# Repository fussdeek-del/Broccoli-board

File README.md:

# Broccoli Board

> A fully wireless 75% mechanical keyboard built from scratch custom PCB, per-key RGB, BLE 5.0, hot-swap switches, and a 3D printed case. Every component chosen, every trace routed by hand.

---

## What is it?

Broccoli Board is a custom 84-key 75% keyboard I designed completely from scratch. The PCB is designed in KiCad, the case in Fusion 360, and the firmware runs on ZMK. It's fully wireless over BLE 5.0 via the nice!nano V2, has per-key RGB LEDs reverse-mounted on the back of the PCB, and uses Kailh hot-swap sockets so I can swap switches without touching a soldering iron.

## Why i built it?
I didn't want to spend $200+ on a keyboard that still isn't fully mine. So I built one my own that belong to me.

---

## Zine

---

## Gallery

### CAD & Assembly
<table>
  <tr>
    <td></td>
    <td></td>
  </tr>
</table>

### PCB
<table>
  <tr>
    <td></td>
    <td></td>
  </tr>
</table>
---

### PCB Soldered

## Features

- 84 keys, 75% layout
- Wireless BLE 5.0 via nice!nano V2 (nRF52840)
- Per-key SK6812 Mini-E RGB reverse mount on B.Cu
- Kailh hot-swap sockets no soldering to swap switches
- Rotary encoder with push switch (EC11)
- USB-C wired + wireless dual mode
- 3.7V LiPo 2000mAh with MCP73831 charger IC
- 74AHCT125 level shifter for LED data
- USBLC6-2SC6 ESD protection on USB lines
- ZMK firmware
- 2-layer PCB, KiCad 10, JLCPCB fabrication
- Custom 3D printed case tray, plate, and bezel

---

## Hardware Specs

| Component | Details |
|---|---|
| MCU | nice!nano V2 (nRF52840), socketed |
| Layout | 75%, 84 keys |
| Switches | Gateron Blue × 84, 5-pin PCB mount |
| Hotswap | Kailh CPG151101S11 × 84 |
| LEDs | SK6812 Mini-E × 84, reverse mount |
| Encoder | EC11 rotary encoder with push switch |
| Wireless | Bluetooth 5.0 BLE |
| Firmware | ZMK |
| Battery | 3.7V LiPo 2000mAh (804050), JST PH2 |
| Charger IC | MCP73831, 500mA |
| Regulator | ME6211 3.3V LDO |
| Level shifter | 74AHCT125 |
| ESD protection | USBLC6-2SC6 |
| USB connector | GCT USB4105, 16-pin USB-C |
| PCB | 2-layer, JLCPCB, KiCad 10 |
| Case | SLA resin 3D print, Fusion 360 |
| Matrix | 9 rows × 10 columns, col2row |

---

## How to Build

### Order the PCB
1. Go to [JLCPCB](https://jlcpcb.com)
2. Upload `pcb/gerbers.zip`
3. 2-layer, FR-4, 1.6mm, HASL or ENIG
4. Minimum order 5 boards

### Flash the Firmware
1. Fork the [ZMK firmware repo](https://github.com/fussdeek-del/Broccoli--board-zmk)
2. Edit keymap at `boards/shields/broccoli_board/broccoli_board.keymap`
3. Push GitHub Actions builds automatically
4. Download `.uf2` from Actions artifacts
5. Double-tap reset on nice!nano to enter bootloader
6. Drag `.uf2` onto the USB drive that appears

note: The frimware isn't completely, i will complete it once this gets approved.

### Assembly Notes
- Solder LEDs on **B.Cu** reverse mount facing down
- Solder hotswap sockets on **F.Cu**
- Solder the nice!nano v2
- Battery connects via JST PH2 to J2

## BOM

> 💰 Estimated total: **~$174 USD** — can drop to **$120–$140** buying locally.

| Component | Spec | Qty | Price | Notes | Link |
|---|---|---|---|---|---|
| Microcontroller (MCU) | nice!nano V2 nRF52840 | ×1 | $7.00 | Clone — cheaper, slightly less reliable | [Buy](https://www.aliexpress.com/item/1005006271881076.html) |
| 74AHCT125 Level Shifter | TSSOP-14 | ×1 | $2.52 | Pack of 10 — LED data 3.3V→5V | [Buy](https://www.aliexpress.com/item/1005008171122183.html) |
| MCP73831 LiPo Charger | SOT-23-5 | ×1 | $2.50 | Pack of 10 — LiPo charging IC | [Buy](https://www.aliexpress.com/item/1005007439657191.html) |
| ME6211 3.3V LDO | ME6211C33 SOT-23-5 | ×1 | $2.20 | Pack of 10 — 3.3V regulator | [Buy](https://www.aliexpress.com/item/1005007315116858.html) |
| USBLC6-2SC6 ESD Protection | SOT-23-6 | ×1 | $1.50 | Pack of 10 — USB ESD protection | [Buy](https://www.aliexpress.com/item/32807108222.html) |
| Gateron Blue Switch | G Pro Blue 5-pin | ×84 | $24.00 | Pack of 100 — 5-pin PCB mount | [Buy](https://www.aliexpress.com/item/1005006091988869.html) |
| Kailh Hotswap Socket | MX compatible | ×84 | $7.00 | Pack of 100 | [Buy](https://www.aliexpress.com/item/1005006105603269.html) |
| EC11 Rotary Encoder | 20mm with push switch | ×1 | $2.00 | Pack of 5 | [Buy](https://www.aliexpress.com/item/1005006460161288.html) |
| Reset Button | SMD tactile 3×4mm | ×1 | $1.50 | Pack of 30 | [Buy](https://www.aliexpress.com/item/4001107416458.html) |
| SK6812 Mini-E RGB LED | Reverse mount | ×84 | $13.50 | Pack of 100 — buy 100, need 84 + spares | [Buy](https://www.aliexpress.com/item/1005004249903121.html) |
| 1N4148W Matrix Diode | SOD-123 | ×84 | $1.50 | Pack of 100 — buy 100, need 84 + spares | [Buy](https://www.aliexpress.com/item/1005010728396328.html) |
| Resistor 10K | 0603 | ×10 | $1.20 | Pack of 300 | [Buy](https://www.aliexpress.com/item/1005011779883974.html) |
| Resistor 5.1K | 0603 | ×5 | $1.30 | Pack of 300 | [Buy](https://www.aliexpress.com/item/1005011779883974.html) |
| Resistor 330Ω | 0603 | ×1 | $2.00 | Pack of 500 | [Buy](https://www.aliexpress.com/item/1005005700395390.html) |
| Capacitor 100nF | 0805 | ×100 | $2.00 | Pack of 200 | [Buy](https://www.aliexpress.com/item/1005007660078779.html) |
| Capacitor 10µF | 0805 | ×1 | $2.20 | Pack of 200 | [Buy](https://www.aliexpress.com/item/1005007660078779.html) |
| USB-C Receptacle 16P | GCT USB4105 SMD | ×1 | $4.50 | Pack of 5 | [Buy](https://www.aliexpress.com/item/1005005581945089.html) |
| JST PH2 2-pin | PH2.0 2-pin connector | ×1 | $2.00 | Pack of 2 | [Buy](https://www.aliexpress.com/item/1005010615395743.html) |
| Polyfuse 500mA | Resettable fuse 1206 | ×1 | $1.70 | Pack of 10 | [Buy](https://www.aliexpress.com/item/1005005235906949.html) |
| LiPo 3.7V 2000mAh | 804050, JST PH | ×1 | $9.40 | Price for 2 | [Buy](https://www.aliexpress.com/item/1005005984841109.html) |
| Keycap Set | PBT 75% MX compatible | ×75 | $22.50 | 100+ keycaps included | [Buy](https://www.aliexpress.com/item/1005007416863215.html) |
| Rotary Knob | Aluminum 6mm D shaft 20mm | ×1 | $2.00 | 2 pieces | [Buy](https://www.aliexpress.com/item/4001091267351.html) |
| PCB Fabrication | 2-layer, FR-4, 1.6mm, HASL | ×5 boards | $22.20 | Minimum 5 pieces | [JLCPCB](https://cart.jlcpcb.com/quote) |
| 3D Print — Tray | SLA resin | ×1 | $25.30 | Local 3D printer recommended | [JLC3DP](https://jlc3dp.com/3d-printing-quote) |
| 3D Print — Top Plate | SLA resin | ×1 | $8.30 | Local 3D printer recommended | [JLC3DP](https://jlc3dp.com/3d-printing-quote) |
| 3D Print — Top Cover | SLA resin | ×1 | $2.65 | Local 3D printer recommended | [JLC3DP](https://jlc3dp.com/3d-printing-quote) |
| M3 Screws | M3 × 8mm countersunk | ×10 | $1.00 | Pack of 50 | [Buy](https://www.aliexpress.com/item/1005008810897680.html) |
| M3 Standoffs | M3 × 4mm | ×10 | $1.00 | Pack of 50 | [Buy](https://www.aliexpress.com/item/1005008810897680.html) |

---
## Schematics note
Schematics is reviewed my multiple people in fallout + AI. there was problem init that i fixed, and now it LGTM
repo is surface checked by riitam
## Credits

- [KiCad](https://www.kicad.org/) — PCB design
- [ZMK Firmware](https://zmk.dev/) — open source keyboard firmware
- [Fusion 360](https://www.autodesk.com/products/fusion-360/) — case design
- [nice!nano](https://nicekeyboards.com/nice-nano/) — nRF52840 BLE module
- [Hack Club Fallout](https://fallout.hackclub.com) — grant that made this real

Made by **Nabeel Ahmed (18) × Hashir (17)** — Punjab, Pakistan 🇵🇰 BWP

---

## License

MIT

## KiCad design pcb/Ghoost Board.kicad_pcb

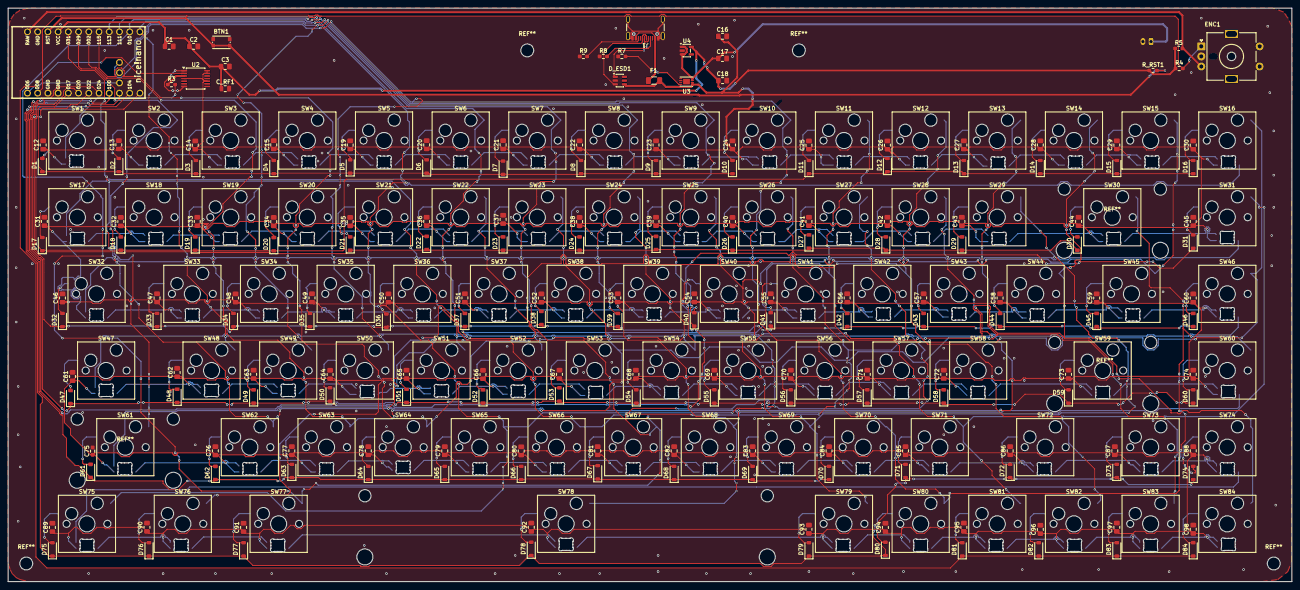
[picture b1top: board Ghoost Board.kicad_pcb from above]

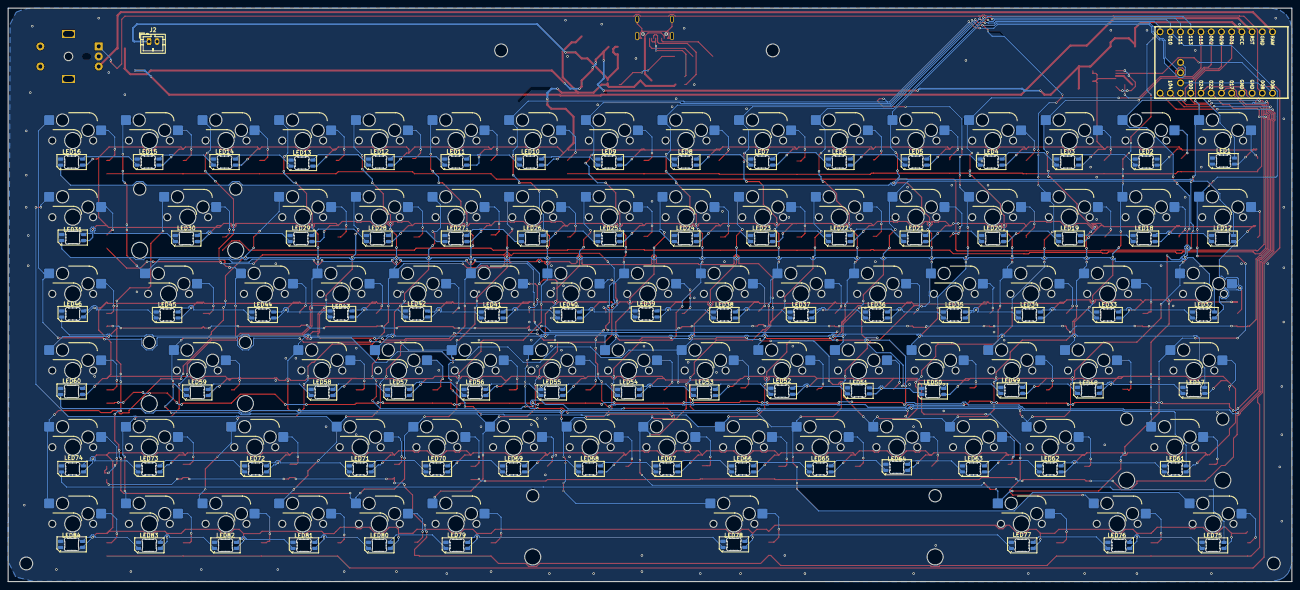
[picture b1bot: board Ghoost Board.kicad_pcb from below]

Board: 2 copper layers, 319.0 x 142.5 mm, 360 parts (85 on the bottom side), 201 nets.

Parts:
BTN1: RESET; SW_Push_1P1T_NO_CK_KMR2
C1, C2, C3, C17, C18: 100nF; C_0805_2012Metric_Pad1.18x1.45mm_HandSolder
C12, C13, C14, C15, C16, C19, C20, C21, C22, C23, C24, C25, C26, C27, C28, C29, C30, C31, C32, C33, C34, C35, C36, C37, C38, C39, C40, C41, C42, C43, C44, C45, C46, C47, C48, C49, C50, C51, C52, C53, C54, C55, C56, C57, C58, C59, C60, C61, C62, C63, C64, C65, C66, C67, C68, C69, C70, C71, C72, C73, C74, C76, C77, C78, C79, C80, C81, C82, C83, C84, C85, C86, C87, C88, C89, C90, C91, C92, C93, C94, C95, C96, C97, C98: 100nf; C_0805_2012Metric_Pad1.18x1.45mm_HandSolder
C75: 100nf; R_0603_1608Metric_Pad0.98x0.95mm_HandSolder
C_RF1: 10uF; C_0805_2012Metric
D1, D2, D3, D4, D5, D6, D7, D8, D9, D10, D11, D12, D13, D14, D15, D16, D17, D18, D19, D20, D21, D22, D23, D24, D25, D26, D27, D28, D29, D30, D31, D32, D33, D34, D35, D36, D37, D38, D39, D40, D41, D42, D43, D44, D45, D46, D47, D48, D49, D50, D51, D52, D53, D54, D55, D56, D57, D58, D59, D60, D61, D62, D63, D64, D65, D66, D67, D68, D69, D70, D71, D72, D73, D74, D75, D76, D77, D78, D79, D80, D81, D82, D83, D84: 1N4148W; D_SOD-123
D_ESD1: USBLC6-2SC6; SOT-23-6
ENC1: EC11; RotaryEncoder_Alps_EC11E-Switch_Vertical_H20mm_MountingHoles
F1: 500mA; Fuse_1206_3216Metric
J1: USB_C_Receptacle_USB2.0_16P; USB_C_Receptacle_GCT_USB4105-xx-A_16P_TopMnt_Horizontal
J2: Battery_JST_PH2; JST_PH_B2B-PH-K_1x02_P2.00mm_Vertical
LED1, LED2, LED3, LED4, LED5, LED6, LED7, LED8, LED9, LED10, LED11, LED12, LED13, LED14, LED15, LED16, LED17, LED18, LED19, LED20, LED21, LED22, LED23, LED24, LED25, LED26, LED27, LED28, LED29, LED30, LED31, LED32, LED33, LED34, LED35, LED36, LED37, LED38, LED39, LED40, LED41, LED42, LED43, LED44, LED45, LED46, LED47, LED48, LED49, LED50, LED51, LED52, LED53, LED54, LED55, LED56, LED57, LED58, LED59, LED60, LED61, LED62, LED63, LED64, LED65, LED66, LED67, LED68, LED69, LED70, LED71, LED72, LED73, LED74, LED75, LED76, LED77, LED78, LED79, LED80, LED81, LED82, LED83, LED84: SK6812Mini-E; LED_SK6812MINI-E_3.2x2.8mm_P1.5mm_ReverseMount
R3: 330R; R_0603_1608Metric_Pad0.98x0.95mm_HandSolder
R4, R5, R7: 10K; R_0603_1608Metric_Pad0.98x0.95mm_HandSolder
R8: 5.1K; R_0603_1608Metric_Pad0.98x0.95mm_HandSolder
R9: 5.1k; R_0603_1608Metric_Pad0.98x0.95mm_HandSolder
R_RST1: 10K; R_0603_1608Metric_Pad0.98x0.95mm_HandSolder
SW1, SW2, SW3, SW4, SW5, SW6, SW7, SW8, SW9, SW10, SW11, SW12, SW13, SW14, SW15, SW16, SW17, SW18, SW19, SW20, SW21, SW22, SW23, SW24, SW25, SW26, SW27, SW28, SW29, SW30, SW31, SW32, SW33, SW34, SW35, SW36, SW37, SW38, SW39, SW40, SW41, SW42, SW43, SW44, SW45, SW46, SW47, SW48, SW49, SW50, SW51, SW52, SW53, SW54, SW55, SW56, SW57, SW58, SW59, SW60, SW61, SW62, SW63, SW64, SW65, SW66, SW67, SW68, SW69, SW70, SW71, SW72, SW73, SW74, SW75, SW76, SW77, SW78, SW79, SW80, SW81, SW82, SW83, SW84: Gateron_Blue; SW_Hotswap_Kailh_MX_1.00u
U1: nice!nano; nice_nano
U2: 74AHCT125; TSSOP-14_4.4x5mm_P0.65mm
U3: MCP73831; DFN-8-1EP_3x2mm_P0.5mm_EP1.7x1.4mm
U4: ME6211-3.3V; SOT-23-5

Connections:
+3.3V: C1.1, C2.1, C3.1, C18.1, C_RF1.1, R4.1, R5.1, R_RST1.1, U1.21 (VCC), U4.5 (V_{OUT})
/COL0: SW1.2, SW11.2, SW21.2, SW31.2, SW41.2, SW51.2, SW61.2, SW71.2, SW81.2, U1.20 (AIN7/P0.31)
/COL1: SW2.2, SW12.2, SW22.2, SW32.2, SW42.2, SW52.2, SW62.2, SW72.2, SW82.2, U1.19 (AIN5/P0.29)
/COL2: SW3.2, SW13.2, SW23.2, SW33.2, SW43.2, SW53.2, SW63.2, SW73.2, SW83.2, U1.18 (AIN0/P0.02)
/COL3: SW4.2, SW14.2, SW24.2, SW34.2, SW44.2, SW54.2, SW64.2, SW74.2, SW84.2, U1.17 (P1.15)
/COL4: SW5.2, SW15.2, SW25.2, SW35.2, SW45.2, SW55.2, SW65.2, SW75.2, U1.16 (P1.13)
/COL5: SW6.2, SW16.2, SW26.2, SW36.2, SW46.2, SW56.2, SW66.2, SW76.2, U1.15 (P1.11)
/COL6: SW7.2, SW17.2, SW27.2, SW37.2, SW47.2, SW57.2, SW67.2, SW77.2, U1.14 (NFC2/P0.10)
/COL7: SW8.2, SW18.2, SW28.2, SW38.2, SW48.2, SW58.2, SW68.2, SW78.2, U1.13 (NFC1/P0.09)
/COL8: SW9.2, SW19.2, SW29.2, SW39.2, SW49.2, SW59.2, SW69.2, SW79.2, U1.32 (P1.02)
/COL9: SW10.2, SW20.2, SW30.2, SW40.2, SW50.2, SW60.2, SW70.2, SW80.2, U1.33 (P1.07)
/ENC_A: ENC1.A, R4.2, U1.2 (RX1/P0.08)
/ENC_B: ENC1.B, R5.2, U1.24 (BATIN/P0.04)
/LED sheets/LED2_DOUT: LED2.1 (DOUT), LED3.3 (DIN)
/LED sheets/LED3_DOUT: LED3.1 (DOUT), LED4.3 (DIN)
/LED sheets/LED4_DOUT: LED4.1 (DOUT), LED5.3 (DIN)
/LED sheets/LED5_DOUT: LED5.1 (DOUT), LED6.3 (DIN)
/LED sheets/LED6_DOUT: LED6.1 (DOUT), LED7.3 (DIN)
/LED sheets/LED7_DOUT: LED7.1 (DOUT), LED8.3 (DIN)
/LED sheets/LED8_DOUT: LED8.1 (DOUT), LED9.3 (DIN)
/LED sheets/LED9_DOUT: LED9.1 (DOUT), LED10.3 (DIN)
/LED sheets/LED10_DOUT: LED10.1 (DOUT), LED11.3 (DIN)
/LED sheets/LED11_DOUT: LED11.1 (DOUT), LED12.3 (DIN)
/LED sheets/LED12_DOUT: LED12.1 (DOUT), LED13.3 (DIN)
/LED sheets/LED13_DOUT: LED13.1 (DOUT), LED14.3 (DIN)
/LED sheets/LED14_DOUT: LED14.1 (DOUT), LED15.3 (DIN)
/LED sheets/LED15_DOUT: LED15.1 (DOUT), LED16.3 (DIN)
/LED sheets/LED16_DOUT: LED16.1 (DOUT), LED17.3 (DIN)
/LED sheets/LED17_DOUT: LED17.1 (DOUT), LED18.3 (DIN)
/LED sheets/LED18_DOUT: LED18.1 (DOUT), LED19.3 (DIN)
/LED sheets/LED19_DOUT: LED19.1 (DOUT), LED20.3 (DIN)
/LED sheets/LED20_DOUT: LED20.1 (DOUT), LED21.3 (DIN)
/LED sheets/LED21_DOUT: LED21.1 (DOUT), LED22.3 (DIN)
/LED sheets/LED22_DOUT: LED22.1 (DOUT), LED23.3 (DIN)
/LED sheets/LED23_DOUT: LED23.1 (DOUT), LED24.3 (DIN)
/LED sheets/LED24_DOUT: LED24.1 (DOUT), LED25.3 (DIN)
/LED sheets/LED25_DOUT: LED25.1 (DOUT), LED26.3 (DIN)
/LED sheets/LED26_DOUT: LED26.1 (DOUT), LED27.3 (DIN)
/LED sheets/LED27_DOUT: LED27.1 (DOUT), LED28.3 (DIN)
/LED sheets/LED28_DOUT: LED28.1 (DOUT), LED29.3 (DIN)
/LED sheets/LED29_DOUT: LED29.1 (DOUT), LED30.3 (DIN)
/LED sheets/LED30_DOUT: LED30.1 (DOUT), LED31.3 (DIN)
/LED sheets/LED31_DOUT: LED31.1 (DOUT), LED32.3 (DIN)
/LED sheets/LED32_DOUT: LED32.1 (DOUT), LED33.3 (DIN)
/LED sheets/LED33_DOUT: LED33.1 (DOUT), LED34.3 (DIN)
/LED sheets/LED34_DOUT: LED34.1 (DOUT), LED35.3 (DIN)
/LED sheets/LED35_DOUT: LED35.1 (DOUT), LED36.3 (DIN)
/LED sheets/LED36_DOUT: LED36.1 (DOUT), LED37.3 (DIN)
/LED sheets/LED37_DOUT: LED37.1 (DOUT), LED38.3 (DIN)
/LED sheets/LED38_DOUT: LED38.1 (DOUT), LED39.3 (DIN)
/LED sheets/LED39_DOUT: LED39.1 (DOUT), LED40.3 (DIN)
/LED sheets/LED40_DOUT: LED40.1 (DOUT), LED41.3 (DIN)
/LED sheets/LED41_DOUT: LED41.1 (DOUT), LED42.3 (DIN)
/LED sheets/LED42_DOUT: LED42.1 (DOUT), LED43.3 (DIN)
/LED sheets/LED43_DOUT: LED43.1 (DOUT), LED44.3 (DIN)
/LED sheets/LED44_DOUT: LED44.1 (DOUT), LED45.3 (DIN)
/LED sheets/LED45_DOUT: LED45.1 (DOUT), LED46.3 (DIN)
/LED sheets/LED46_DOUT: LED46.1 (DOUT), LED47.3 (DIN)
/LED sheets/LED47_DOUT: LED47.1 (DOUT), LED48.3 (DIN)
/LED sheets/LED48_DOUT: LED48.1 (DOUT), LED49.3 (DIN)
/LED sheets/LED49_DOUT: LED49.1 (DOUT), LED50.3 (DIN)
/LED sheets/LED50_DOUT: LED50.1 (DOUT), LED51.3 (DIN)
/LED sheets/LED51_DOUT: LED51.1 (DOUT), LED52.3 (DIN)
/LED sheets/LED52_DOUT: LED52.1 (DOUT), LED53.3 (DIN)
/LED sheets/LED53_DOUT: LED53.1 (DOUT), LED54.3 (DIN)
/LED sheets/LED54_DOUT: LED54.1 (DOUT), LED55.3 (DIN)
/LED sheets/LED55_DOUT: LED55.1 (DOUT), LED56.3 (DIN)
/LED sheets/LED56_DOUT: LED56.1 (DOUT), LED57.3 (DIN)
/LED sheets/LED57_DOUT: LED57.1 (DOUT), LED58.3 (DIN)
/LED sheets/LED58_DOUT: LED58.1 (DOUT), LED59.3 (DIN)
/LED sheets/LED59_DOUT: LED59.1 (DOUT), LED60.3 (DIN)
/LED sheets/LED60_DOUT: LED60.1 (DOUT), LED61.3 (DIN)
/LED sheets/LED61_DOUT: LED61.1 (DOUT), LED62.3 (DIN)
/LED sheets/LED62_DOUT: LED62.1 (DOUT), LED63.3 (DIN)
/LED sheets/LED63_DOUT: LED63.1 (DOUT), LED64.3 (DIN)
/LED sheets/LED64_DOUT: LED64.1 (DOUT), LED65.3 (DIN)
/LED sheets/LED65_DOUT: LED65.1 (DOUT), LED66.3 (DIN)
/LED sheets/LED66_DOUT: LED66.1 (DOUT), LED67.3 (DIN)
/LED sheets/LED67_DOUT: LED67.1 (DOUT), LED68.3 (DIN)
/LED sheets/LED68_DOUT: LED68.1 (DOUT), LED69.3 (DIN)
/LED sheets/LED69_DOUT: LED69.1 (DOUT), LED70.3 (DIN)
/LED sheets/LED70_DOUT: LED70.1 (DOUT), LED71.3 (DIN)
/LED sheets/LED71_DOUT: LED71.1 (DOUT), LED72.3 (DIN)
/LED sheets/LED72_DOUT: LED72.1 (DOUT), LED73.3 (DIN)
/LED sheets/LED73_DOUT: LED73.1 (DOUT), LED74.3 (DIN)
/LED sheets/LED74_DOUT: LED74.1 (DOUT), LED75.3 (DIN)
/LED sheets/LED75_DOUT: LED75.1 (DOUT), LED76.3 (DIN)
/LED sheets/LED76_DOUT: LED76.1 (DOUT), LED77.3 (DIN)
/LED sheets/LED77_DOUT: LED77.1 (DOUT), LED78.3 (DIN)
/LED sheets/LED78_DOUT: LED78.1 (DOUT), LED79.3 (DIN)
/LED sheets/LED79_DOUT: LED79.1 (DOUT), LED80.3 (DIN)
/LED sheets/LED80_DOUT: LED80.1 (DOUT), LED81.3 (DIN)
/LED sheets/LED81_DOUT: LED81.1 (DOUT), LED82.3 (DIN)
/LED sheets/LED82_DOUT: LED82.1 (DOUT), LED83.3 (DIN)
/LED sheets/LED83_DOUT: LED83.1 (DOUT), LED84.3 (DIN)
/LED_DATA_3V3: U1.1 (TX0/P0.06), U2.2
/LED_DATA_5V: R3.1, U2.3
/LED_DATA_OUT: LED1.3 (DIN), R3.2
/RESET: BTN1.2, R_RST1.2, U1.22 (RST)
/ROW0: D1.1 (K), D2.1 (K), D3.1 (K), D4.1 (K), D5.1 (K), D6.1 (K), D7.1 (K), D8.1 (K), D9.1 (K), D10.1 (K), U1.5 (P0.17)
/ROW1: D11.1 (K), D12.1 (K), D13.1 (K), D14.1 (K), D15.1 (K), D16.1 (K), D17.1 (K), D18.1 (K), D19.1 (K), D20.1 (K), U1.6 (P0.20)
/ROW2: D21.1 (K), D22.1 (K), D23.1 (K), D24.1 (K), D25.1 (K), D26.1 (K), D27.1 (K), D28.1 (K), D29.1 (K), D30.1 (K), U1.7 (P0.22)
/ROW3: D31.1 (K), D32.1 (K), D33.1 (K), D34.1 (K), D35.1 (K), D36.1 (K), D37.1 (K), D38.1 (K), D39.1 (K), D40.1 (K), U1.8 (P0.24)
/ROW4: D41.1 (K), D42.1 (K), D43.1 (K), D44.1 (K), D45.1 (K), D46.1 (K), D47.1 (K), D48.1 (K), D49.1 (K), D50.1 (K), U1.9 (P1.00)
/ROW5: D51.1 (K), D52.1 (K), D53.1 (K), D54.1 (K), D55.1 (K), D56.1 (K), D57.1 (K), D58.1 (K), D59.1 (K), D60.1 (K), U1.10 (P0.11)
/ROW6: D61.1 (K), D62.1 (K), D63.1 (K), D64.1 (K), D65.1 (K), D66.1 (K), D67.1 (K), D68.1 (K), D69.1 (K), D70.1 (K), U1.11 (P1.04)
/ROW7: D71.1 (K), D72.1 (K), D73.1 (K), D74.1 (K), D75.1 (K), D76.1 (K), D77.1 (K), D78.1 (K), D79.1 (K), D80.1 (K), U1.12 (P1.06)
/ROW8: D81.1 (K), D82.1 (K), D83.1 (K), D84.1 (K), U1.31 (P1.01)
/USB_DN: D_ESD1.1 (I/O1), J1.A7 (D-), J1.B7 (D-)
/USB_DP: D_ESD1.3 (I/O2), J1.A6 (D+), J1.B6 (D+)
/VBAT: C17.1, J2.1, U3.3 (V_{BAT}), U3.4 (V_{BAT}), U4.1 (V_{IN}), U4.3 (CE)
/VBUS_IN: F1.1, J1.A4 (VBUS), J1.A9 (VBUS), J1.B4 (VBUS), J1.B9 (VBUS)
GND: BTN1.1, C1.2, C2.2, C3.2, C12.2, C13.2, C14.2, C15.2, C16.2, C17.2, C18.2, C19.2, C20.2, C21.2, C22.2, C23.2, C24.2, C25.2, C26.2, C27.2, C28.2, C29.2, C30.2, C31.2, C32.2, C33.2, C34.2, C35.2, C36.2, C37.2, C38.2, C39.2, C40.2, C41.2, C42.2, C43.2, C44.2, C45.2, C46.2, C47.2, C48.2, C49.2, C50.2, C51.2, C52.2, C53.2, C54.2, C55.2, C56.2, C57.2, C58.2, C59.2, C60.2, C61.2, C62.2, C63.2, C64.2, C65.2, C66.2, C67.2, C68.2, C69.2, C70.2, C71.2, C72.2, C73.2, C74.2, C75.2, C76.2, C77.2, C78.2, C79.2, C80.2, C81.2, C82.2, C83.2, C84.2, C85.2, C86.2, C87.2, C88.2, C89.2, C90.2, C91.2, C92.2, C93.2, C94.2, C95.2, C96.2, C97.2, C98.2, C_RF1.2, D_ESD1.2 (GND), ENC1.C, J1.A1 (GND), J1.A12 (GND), J1.B1 (GND), J1.B12 (GND), J1.SH (SHIELD), J2.2, LED1.2 (VSS), LED2.2 (VSS), LED3.2 (VSS), LED4.2 (VSS), LED5.2 (VSS), LED6.2 (VSS), LED7.2 (VSS), LED8.2 (VSS), LED9.2 (VSS), LED10.2 (VSS), LED11.2 (VSS), LED12.2 (VSS), LED13.2 (VSS), LED14.2 (VSS), LED15.2 (VSS), LED16.2 (VSS), LED17.2 (VSS), LED18.2 (VSS), LED19.2 (VSS), LED20.2 (VSS), LED21.2 (VSS), LED22.2 (VSS), LED23.2 (VSS), LED24.2 (VSS), LED25.2 (VSS), LED26.2 (VSS), LED27.2 (VSS), LED28.2 (VSS), LED29.2 (VSS), LED30.2 (VSS), LED31.2 (VSS), LED32.2 (VSS), LED33.2 (VSS), LED34.2 (VSS), LED35.2 (VSS), LED36.2 (VSS), LED37.2 (VSS), LED38.2 (VSS), LED39.2 (VSS), LED40.2 (VSS), LED41.2 (VSS), LED42.2 (VSS), LED43.2 (VSS), LED44.2 (VSS), LED45.2 (VSS), LED46.2 (VSS), LED47.2 (VSS), LED48.2 (VSS), LED49.2 (VSS), LED50.2 (VSS), LED51.2 (VSS), LED52.2 (VSS), LED53.2 (VSS), LED54.2 (VSS), LED55.2 (VSS), LED56.2 (VSS), LED57.2 (VSS), LED58.2 (VSS), LED59.2 (VSS), LED60.2 (VSS), LED61.2 (VSS), LED62.2 (VSS), LED63.2 (VSS), LED64.2 (VSS), LED65.2 (VSS), LED66.2 (VSS), LED67.2 (VSS), LED68.2 (VSS), LED69.2 (VSS), LED70.2 (VSS), LED71.2 (VSS), LED72.2 (VSS), LED73.2 (VSS), LED74.2 (VSS), LED75.2 (VSS), LED76.2 (VSS), LED77.2 (VSS), LED78.2 (VSS), LED79.2 (VSS), LED80.2 (VSS), LED81.2 (VSS), LED82.2 (VSS), LED83.2 (VSS), LED84.2 (VSS), R7.1, R8.1, R9.1, U1.3 (GND), U1.4 (GND), U1.23 (GND), U2.1, U2.7 (GND), U3.6 (V_{SS}), U4.2 (V_{SS})
unnamed: D1.2 (A), SW1.1
unnamed: D2.2 (A), SW2.1
unnamed: D3.2 (A), SW3.1
unnamed: D4.2 (A), SW4.1
unnamed: D5.2 (A), SW5.1
unnamed: D6.2 (A), SW6.1
unnamed: D7.2 (A), SW7.1
unnamed: D8.2 (A), SW8.1
unnamed: D9.2 (A), SW9.1
unnamed: D10.2 (A), SW10.1
unnamed: D11.2 (A), SW11.1
unnamed: D12.2 (A), SW12.1
unnamed: D13.2 (A), SW13.1
unnamed: D14.2 (A), SW14.1
unnamed: D15.2 (A), SW15.1
unnamed: D16.2 (A), SW16.1
unnamed: D17.2 (A), SW17.1
unnamed: D18.2 (A), SW18.1
unnamed: D19.2 (A), SW19.1
unnamed: D20.2 (A), SW20.1
unnamed: D21.2 (A), SW21.1
unnamed: D22.2 (A), SW22.1
unnamed: D23.2 (A), SW23.1
unnamed: D24.2 (A), SW24.1
unnamed: D25.2 (A), SW25.1
unnamed: D26.2 (A), SW26.1
unnamed: D27.2 (A), SW27.1
unnamed: D28.2 (A), SW28.1
unnamed: D29.2 (A), SW29.1
unnamed: D30.2 (A), SW30.1
unnamed: D31.2 (A), SW31.1
unnamed: D32.2 (A), SW32.1
unnamed: D33.2 (A), SW33.1
unnamed: D34.2 (A), SW34.1
unnamed: D35.2 (A), SW35.1
unnamed: D36.2 (A), SW36.1
unnamed: D37.2 (A), SW37.1
unnamed: D38.2 (A), SW38.1
unnamed: D39.2 (A), SW39.1
unnamed: D40.2 (A), SW40.1
unnamed: D41.2 (A), SW41.1
unnamed: D42.2 (A), SW42.1
unnamed: D43.2 (A), SW43.1
unnamed: D44.2 (A), SW44.1
unnamed: D45.2 (A), SW45.1
unnamed: D46.2 (A), SW46.1
unnamed: D47.2 (A), SW47.1
unnamed: D48.2 (A), SW48.1
unnamed: D49.2 (A), SW49.1
unnamed: D50.2 (A), SW50.1
unnamed: D51.2 (A), SW51.1
unnamed: D52.2 (A), SW52.1
unnamed: D53.2 (A), SW53.1
unnamed: D54.2 (A), SW54.1
unnamed: D55.2 (A), SW55.1
unnamed: D56.2 (A), SW56.1
unnamed: D57.2 (A), SW57.1
unnamed: D58.2 (A), SW58.1
unnamed: D59.2 (A), SW59.1
unnamed: D60.2 (A), SW60.1
unnamed: D61.2 (A), SW61.1
unnamed: D62.2 (A), SW62.1
unnamed: D63.2 (A), SW63.1
unnamed: D64.2 (A), SW64.1
unnamed: D65.2 (A), SW65.1
unnamed: D66.2 (A), SW66.1
unnamed: D67.2 (A), SW67.1
unnamed: D68.2 (A), SW68.1
unnamed: D69.2 (A), SW69.1
unnamed: D70.2 (A), SW70.1
unnamed: D71.2 (A), SW71.1
unnamed: D72.2 (A), SW72.1
unnamed: D73.2 (A), SW73.1
unnamed: D74.2 (A), SW74.1
unnamed: D75.2 (A), SW75.1
unnamed: D76.2 (A), SW76.1
unnamed: D77.2 (A), SW77.1
unnamed: D78.2 (A), SW78.1
unnamed: D79.2 (A), SW79.1
unnamed: D80.2 (A), SW80.1
unnamed: D81.2 (A), SW81.1
unnamed: D82.2 (A), SW82.1
unnamed: D83.2 (A), SW83.1
unnamed: D84.2 (A), SW84.1
unnamed: J1.A5 (CC1), R8.2
unnamed: J1.B5 (CC2), R9.2
unnamed: R7.2, U3.8 (PROG)
VBUS: C12.1, C13.1, C14.1, C15.1, C16.1, C19.1, C20.1, C21.1, C22.1, C23.1, C24.1, C25.1, C26.1, C27.1, C28.1, C29.1, C30.1, C31.1, C32.1, C33.1, C34.1, C35.1, C36.1, C37.1, C38.1, C39.1, C40.1, C41.1, C42.1, C43.1, C44.1, C45.1, C46.1, C47.1, C48.1, C49.1, C50.1, C51.1, C52.1, C53.1, C54.1, C55.1, C56.1, C57.1, C58.1, C59.1, C60.1, C61.1, C62.1, C63.1, C64.1, C65.1, C66.1, C67.1, C68.1, C69.1, C70.1, C71.1, C72.1, C73.1, C74.1, C75.1, C76.1, C77.1, C78.1, C79.1, C80.1, C81.1, C82.1, C83.1, C84.1, C85.1, C86.1, C87.1, C88.1, C89.1, C90.1, C91.1, C92.1, C93.1, C94.1, C95.1, C96.1, C97.1, C98.1, D_ESD1.4 (I/O2), F1.2, LED1.4 (VDD), LED2.4 (VDD), LED3.4 (VDD), LED4.4 (VDD), LED5.4 (VDD), LED6.4 (VDD), LED7.4 (VDD), LED8.4 (VDD), LED9.4 (VDD), LED10.4 (VDD), LED11.4 (VDD), LED12.4 (VDD), LED13.4 (VDD), LED14.4 (VDD), LED15.4 (VDD), LED16.4 (VDD), LED17.4 (VDD), LED18.4 (VDD), LED19.4 (VDD), LED20.4 (VDD), LED21.4 (VDD), LED22.4 (VDD), LED23.4 (VDD), LED24.4 (VDD), LED25.4 (VDD), LED26.4 (VDD), LED27.4 (VDD), LED28.4 (VDD), LED29.4 (VDD), LED30.4 (VDD), LED31.4 (VDD), LED32.4 (VDD), LED33.4 (VDD), LED34.4 (VDD), LED35.4 (VDD), LED36.4 (VDD), LED37.4 (VDD), LED38.4 (VDD), LED39.4 (VDD), LED40.4 (VDD), LED41.4 (VDD), LED42.4 (VDD), LED43.4 (VDD), LED44.4 (VDD), LED45.4 (VDD), LED46.4 (VDD), LED47.4 (VDD), LED48.4 (VDD), LED49.4 (VDD), LED50.4 (VDD), LED51.4 (VDD), LED52.4 (VDD), LED53.4 (VDD), LED54.4 (VDD), LED55.4 (VDD), LED56.4 (VDD), LED57.4 (VDD), LED58.4 (VDD), LED59.4 (VDD), LED60.4 (VDD), LED61.4 (VDD), LED62.4 (VDD), LED63.4 (VDD), LED64.4 (VDD), LED65.4 (VDD), LED66.4 (VDD), LED67.4 (VDD), LED68.4 (VDD), LED69.4 (VDD), LED70.4 (VDD), LED71.4 (VDD), LED72.4 (VDD), LED73.4 (VDD), LED74.4 (VDD), LED75.4 (VDD), LED76.4 (VDD), LED77.4 (VDD), LED78.4 (VDD), LED79.4 (VDD), LED80.4 (VDD), LED81.4 (VDD), LED82.4 (VDD), LED83.4 (VDD), LED84.4 (VDD), U2.4, U2.10, U2.13, U2.14 (VCC), U3.1 (V_{DD}), U3.2 (V_{DD})

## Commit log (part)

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2026-05-05 Add all project files
2026-05-05 Revise repo structure details in README
    Updated the repository structure section in README.md.
2026-05-05 Revise README.md for clarity and updates
    Updated sections for Hardware, How to use, Repo structure, and Zine page in README.md.
2026-05-06 almost done
2026-05-07 Revise README for Broccoli Board project
    Updated README.md for clarity and detail on the Broccoli Board project, including hardware specs, build instructions, and repo structure.
2026-05-07 almost
2026-05-07 Fix image filename for full assembly demo
2026-05-07 Fix image paths in README.md
    Updated image paths in README for better formatting.
2026-05-07 Update image format for PCB F.cu in README
2026-05-07 Update README to remove repo structure details
    Removed repo structure section from README.
2026-05-07 alomost done
2026-05-07 Update README with reasons for building and image cleanup
    Added a section explaining the reason for building the keyboard and removed AI generated renders and several images from the gallery.
2026-05-07 Clean up README by removing unnecessary content
    Removed incomplete firmware note and extraneous lines.
2026-05-07 Enhance BOM section with detailed component info
    Updated the Bill of Materials (BOM) section with detailed component specifications, quantities, prices, and purchase links.
2026-05-07 Update gallery section to use tables for images
    Replaced images with a table format for better layout.
2026-05-07 cad file added
2026-05-07 Update README with schematics note
    Added a note about schematics review and fixed issues.
2026-05-08 Update price of nice!nano V2 nRF52840 in README
    Updated the price of the nice!nano V2 nRF52840 microcontroller from $5.00 to $7.00.
2026-05-08 img added
2026-05-10 Update reason for building the keyboard
    Clarified the reason for building the keyboard and added a humorous note.
2026-06-12 Add 'BWP' to credits in README
    Updated the README to include 'BWP' in the credits.
2026-06-26 ggyayay
